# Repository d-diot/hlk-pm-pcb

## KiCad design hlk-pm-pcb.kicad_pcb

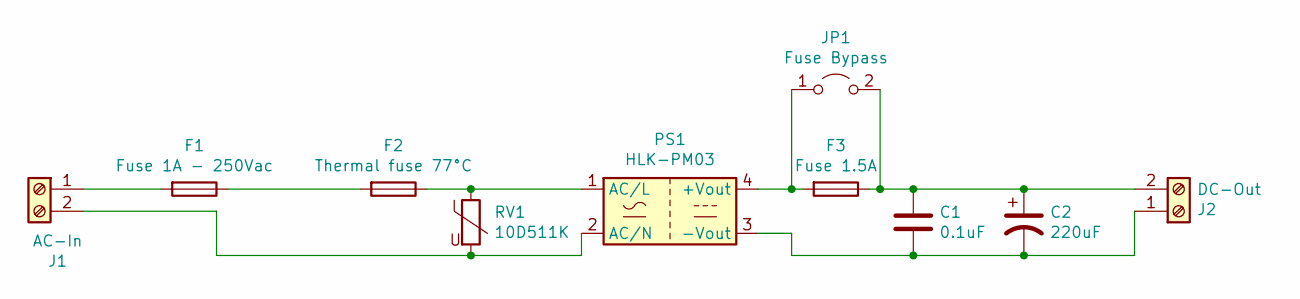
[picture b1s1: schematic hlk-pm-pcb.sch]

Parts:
C1: 0.1uF; C_0805_2012Metric; MPN 0805B104K500NT
C2: 220uF; CP_Elec_8x10.5; MPN CS1E221M-CRF10
F1: Fuse 1A - 250Vac; Fuseholder_Cylinder-5x20mm_Schurter_0031_8201_Horizontal_Op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; MPN C58066
F2: Thermal fuse 77°C; R_Axial_DIN0516_L15.5mm_D5.0mm_P25.40mm_Horizontal; MPN BTT010077
F3: Fuse 1.5A; Fuse_1206_3216Metric; MPN 12D1150C
J1: AC-In; TerminalBlock_bornier-2_P5.08mm; MPN KF127-5.08-2P
J2: DC-Out; TerminalBlock_bornier-2_P5.08mm; MPN KF127-5.08-2P
JP1: Fuse Bypass; SolderJumper-2_P1.3mm_Open_TrianglePad1.0x1.5mm; MPN NA
PS1: HLK-PM03; Converter_ACDC_HiLink_HLK-PMxx; MPN HLK-PM03
RV1: 10D511K; RV_Disc_D12mm_W6.2mm_P7.5mm; MPN VDR-10D511K

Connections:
unnamed: C1.1, C2.1, F3.1, J2.2, JP1.2 (B)
unnamed: C1.2, C2.2, J2.1, PS1.3 (-Vout)
unnamed: F1.1, F2.2
unnamed: F1.2, J1.1
unnamed: F2.1, PS1.1 (AC/L), RV1.1
unnamed: F3.2, JP1.1 (A), PS1.4 (+Vout)
unnamed: J1.2, PS1.2 (AC/N), RV1.2

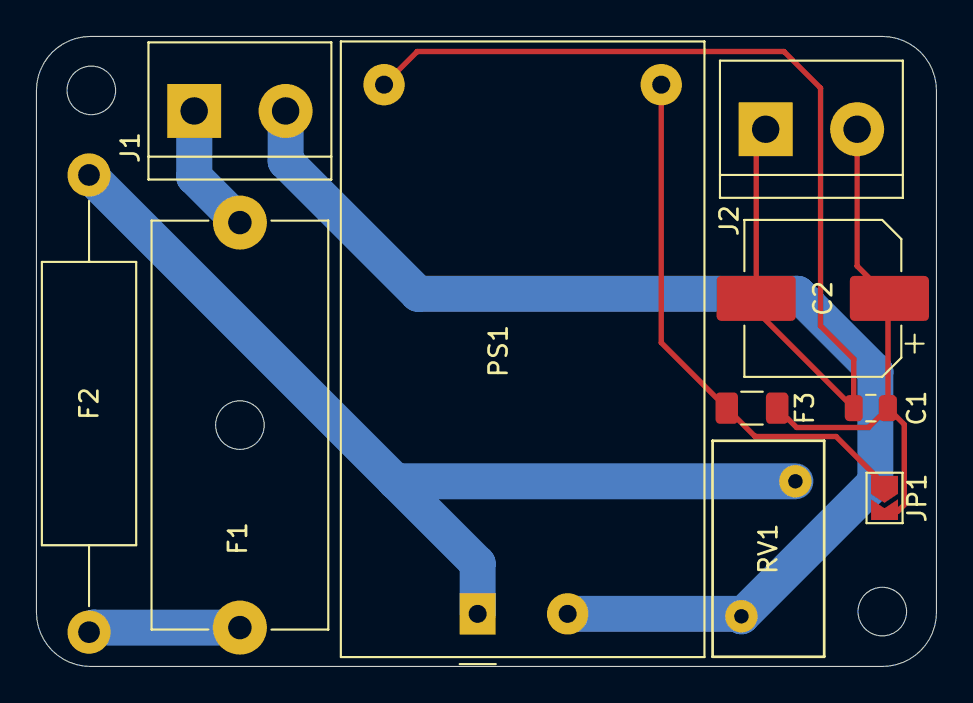
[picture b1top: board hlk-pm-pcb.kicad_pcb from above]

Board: 2 copper layers, 50.0 x 35.0 mm, 10 parts (0 on the bottom side), 7 nets.

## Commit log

2022-01-08 development
2022-01-09 Release board v.1.0
